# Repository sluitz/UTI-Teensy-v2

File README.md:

# UTI-Teensy-v2

PCB designs, Teensy code, and PCB enclosure designs for a UTI- and Teensy 4.1-based cryogenic-temperature-compatible liquid-level sensor.

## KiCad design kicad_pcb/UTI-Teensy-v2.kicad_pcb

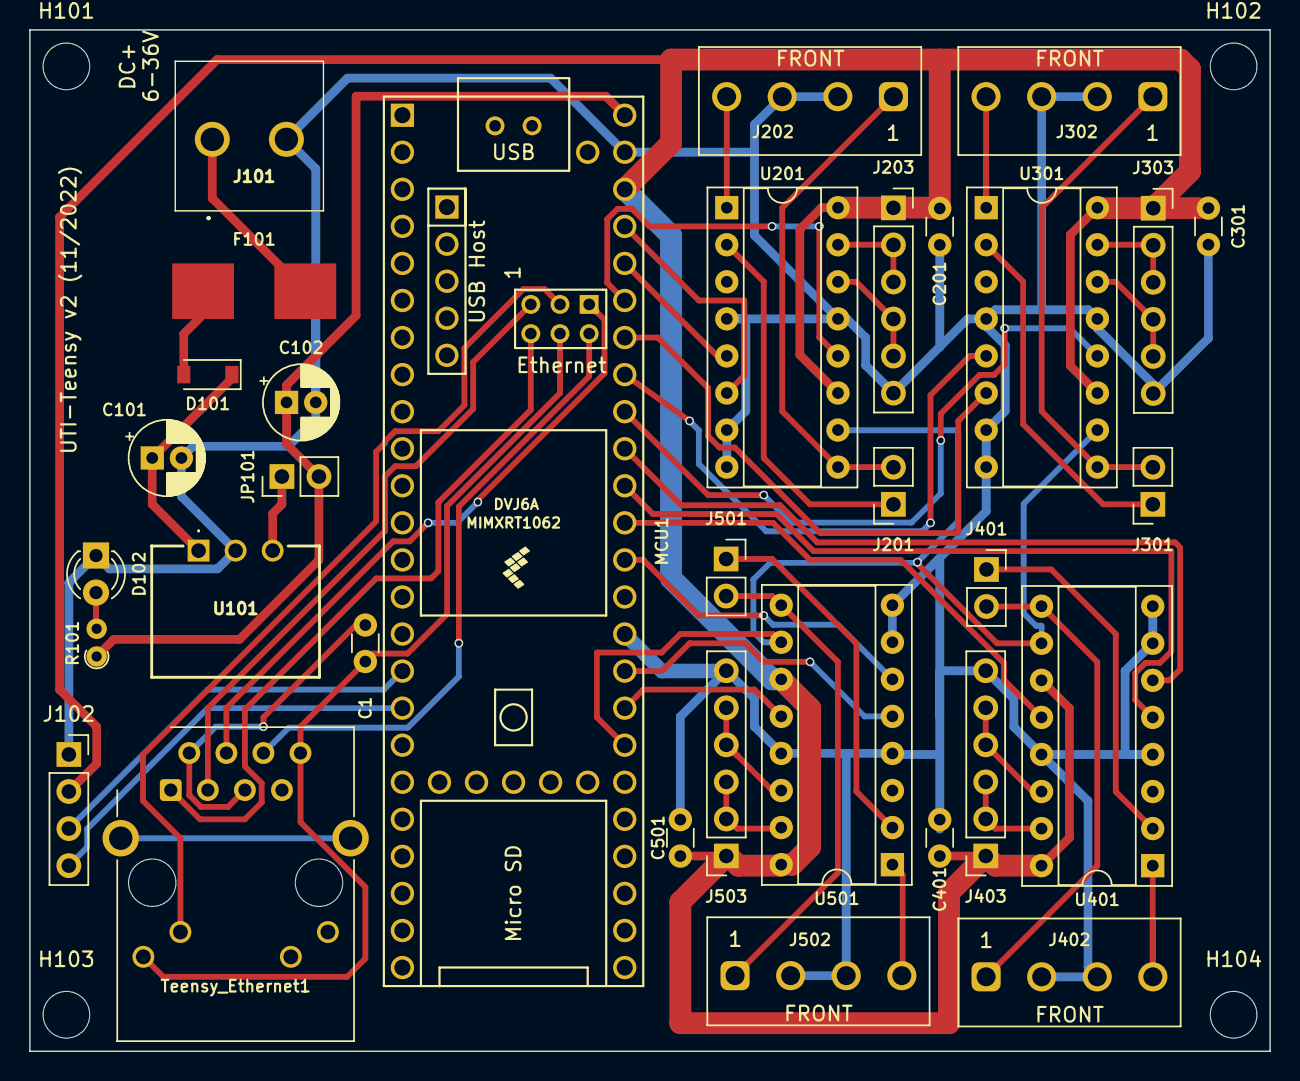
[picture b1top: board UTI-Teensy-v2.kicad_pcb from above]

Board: 2 copper layers, 85.0 x 70.0 mm, 37 parts (0 on the bottom side), 50 nets.

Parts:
C1: 0.1uF1; C_Disc_D3.0mm_W1.6mm_P2.50mm
C101: 10u; CP_Radial_D5.0mm_P2.00mm
C102: 22u; CP_Radial_D5.0mm_P2.00mm
C201, C301, C401, C501: 0.1uF; C_Disc_D3.0mm_W1.6mm_P2.50mm
D101: D; D_SOD-123
D102: LED 5VOK; LED_D3.0mm
F101: 1A; smd_fuse
H101, H102, H103, H104: MountingHole; MountingHole_3.2mm_M3_DIN965
J101: PwrIn; TB00750802BE
J102: OLED Display I2C; PinSocket_1x04_P2.54mm_Vertical
J201, J301, J401, J501: Cref; PinSocket_1x02_P2.54mm_Vertical
J202, J302, J402, J502: C_x; Amphenol Anytech YO 3.81mm 4p
J203, J303, J403, J503: extR; PinSocket_1x06_P2.54mm_Vertical
JP101: PS; PinHeader_1x02_P2.54mm_Vertical
MCU1: Teensy4.1; Teensy41
R101: 330R; R_Axial_DIN0204_L3.6mm_D1.6mm_P1.90mm_Vertical
Teensy_Ethernet1: RJ45_LED; RJ45_Cetus_J1B1211CCD_Horizontal
U101: N7805; N78051C
U201, U301, U401, U501: UTI-DIL16; DIP-16_W7.62mm_Socket

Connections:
+3.3V: C201.1, C301.1, C401.1, C501.1, J102.2, J203.1, J303.1, J403.1, J503.1, MCU1.46 (3V3), U201.11 (PD), U201.16 (VDD), U301.11 (PD), U301.16 (VDD), U401.11 (PD), U401.16 (VDD), U501.11 (PD), U501.16 (VDD)
+5V: C102.1, JP101.2 (B), MCU1.48 (VIN), R101.1
+6-36V: F101.2, J101.1
/UTI+Connectors1/OUT: MCU1.43 (21_A7_RX5_BCLK1), U201.12 (OUT)
/UTI+Connectors1/SEL2: MCU1.44 (22_A8_CTX1), U201.5 (SEL2)
/UTI+Connectors1/SEL3: MCU1.45 (23_A9_CRX1_MCLK1), U201.6 (SEL3)
/UTI+Connectors2/OUT: MCU1.40 (18_A4_SDA), U301.12 (OUT)
/UTI+Connectors2/SEL2: MCU1.41 (19_A5_SCL), U301.5 (SEL2)
/UTI+Connectors2/SEL3: MCU1.42 (20_A6_TX5_LRCLK1), U301.6 (SEL3)
/UTI+Connectors3/OUT: MCU1.37 (15_A1_RX3_SPDIF_IN), U401.12 (OUT)
/UTI+Connectors3/SEL2: MCU1.38 (16_A2_RX4_SCL1), U401.5 (SEL2)
/UTI+Connectors3/SEL3: MCU1.39 (17_A3_TX4_SDA1), U401.6 (SEL3)
/UTI+Connectors4/OUT: MCU1.32 (40_A16), U501.12 (OUT)
/UTI+Connectors4/SEL2: MCU1.33 (41_A17), U501.5 (SEL2)
/UTI+Connectors4/SEL3: MCU1.36 (14_A0_TX3_SPDIF_OUT), U501.6 (SEL3)
GND: C101.2, C102.2, C201.2, C301.2, C401.2, C501.2, D102.1 (K), J101.2, J102.1, J202.2, J202.3, J203.6, J302.2, J302.3, J303.6, J402.2, J402.3, J403.6, J502.2, J502.3, J503.6, MCU1.34 (GND), MCU1.47 (GND), U101.2 (GND/-Vout), U201.4 (SEL1), U201.7 (SEL4), U201.8 (VSS), U201.13 (CML), U301.4 (SEL1), U301.7 (SEL4), U301.8 (VSS), U301.13 (CML), U401.4 (SEL1), U401.7 (SEL4), U401.8 (VSS), U401.13 (CML), U501.4 (SEL1), U501.7 (SEL4), U501.8 (VSS), U501.13 (CML)
I2C_SCL: J102.3, MCU1.16 (24_A10_TX6_SCL2)
I2C_SDA: J102.4, MCU1.17 (25_A11_RX6_SDA2)
unnamed: C1.1, Teensy_Ethernet1.2, Teensy_Ethernet1.5
unnamed: C1.2, MCU1.64 (GND), Teensy_Ethernet1.8, Teensy_Ethernet1.9
unnamed: C101.1, D101.1 (K), U101.1 (IN)
unnamed: D101.2 (A), F101.1
unnamed: D102.2 (A), R101.2
unnamed: J201.1, U201.2 (C)
unnamed: J201.2, J202.1, U201.9 (A)
unnamed: J202.4, U201.1 (D)
unnamed: J203.2, J203.3, U201.15 (E)
unnamed: J203.4, J203.5, U201.14 (F)
unnamed: J301.1, U301.2 (C)
unnamed: J301.2, J302.1, U301.9 (A)
unnamed: J302.4, U301.1 (D)
unnamed: J303.2, J303.3, U301.15 (E)
unnamed: J303.4, J303.5, U301.14 (F)
unnamed: J401.1, U401.2 (C)
unnamed: J401.2, J402.1, U401.9 (A)
unnamed: J402.4, U401.1 (D)
unnamed: J403.2, J403.3, U401.15 (E)
unnamed: J403.4, J403.5, U401.14 (F)
unnamed: J501.1, U501.2 (C)
unnamed: J501.2, J502.1, U501.9 (A)
unnamed: J502.4, U501.1 (D)
unnamed: J503.2, J503.3, U501.15 (E)
unnamed: J503.4, J503.5, U501.14 (F)
unnamed: JP101.1 (A), U101.3 (+Vout/GND)
unnamed: MCU1.60 (R+), Teensy_Ethernet1.4
unnamed: MCU1.61 (LED), Teensy_Ethernet1.10
unnamed: MCU1.62 (T-), Teensy_Ethernet1.3
unnamed: MCU1.63 (T+), Teensy_Ethernet1.1
unnamed: MCU1.65 (R-), Teensy_Ethernet1.6
SF: MCU1.31 (39_MISO1_OUT1A), U201.10 (SF), U301.10 (SF), U401.10 (SF), U501.10 (SF)

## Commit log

2022-12-02 UTI-Teensy-v2 initial commit
2022-12-06 Update read-uti-teensy-interrupt.ino
    lots of changes, primarily for outputting more values to modbus and removing hardcoded constants.
2022-12-08 Enclosure for the PCB
    The design files for an enclosure for the PCB, courtesy of Marshall Johnson. (Uploaded with permission.)
2022-12-08 Update README.md
    Make it more legible.
2022-12-08 PCB Enclosure, courtesy of Marshall Johnson
2022-12-09 Update read-uti-teensy-interrupt.ino
    blink the LED a few times before starting
